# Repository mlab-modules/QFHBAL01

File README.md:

# QFHBAL01 - Antenna Interface and Balun

The **QFHBAL01** module is an [antenna interface and balun](https://en.wikipedia.org/wiki/Balun) designed for QFH (Quadrifilar Helix) antennas, supporting right-hand (RHCP) and left-hand circular polarizations (LHCP). This module enables efficient impedance matching and balanced transmission in QFH antenna configurations.

## Key Features

- **Polarization**: RHCP and LHCP
- **Frequency Range**: 4.5 - 3000 MHz
- **Insertion Loss**: 2 dB typical
- **Amplitude Balance**: ±1 dB
- **Phase Balance**: ±20°
- **Power Rating**: 250 mW max RF, 30 mA max DC
- **Operating Temperature**: -55 °C to +85 °C
- **Dimensions**: Diameter 32 mm, Height 20 mm
- **Weight**: 10 g

## Transformer Mounting Options

The **ETC1-1-13** transformer on the QFHBAL01 module can be soldered onto the PCB in two configurations:

1. **Galvanic Isolation**: Isolates the antenna from the RF line, enhancing protection for the receiver input but potentially increasing insertion loss slightly.
2. **Direct Galvanic Connection**: Connects the antenna directly to the RF line without isolation, minimizing insertion loss but offering less protection for the receiver input.

These configurations allow customization based on application requirements for input protection and insertion loss.

### Balun Polarization and Connection

| Helices     | Feedpoint      | Radiation | Polarization |
|-------------|----------------|-----------|--------------|
| Left-hand   | Standard       | Upward    | RHCP         |
| Right-hand  | Anti-standard  | Upward    | LHCP         |
| Left-hand   | Anti-standard  | Downward  | RHCP         |
| Right-hand  | Standard       | Downward  | LHCP         |

*Source: [QHA Simulation](https://uuki.kapsi.fi/qha_simul.html)*

## Schematic and Mechanical Drawing

- [Schematic (PDF)](/doc/gen/QFHBAL01-schematic.pdf)
- [Mechanical Drawing (PDF)](/doc/src/img/dimensions.png)

### ETC1-1-13 Transformer Specifications

The **ETC1-1-13** transformer offers a 1:1 impedance ratio suitable for balanced RF transmission:

- **Frequency Range**: 4.5 - 3000 MHz
- **Insertion Loss**: 0.32 dB typical, max 3.5 dB at high frequencies
- **Amplitude Balance**: ±1 dB
- **Phase Balance**: ±20°
- **Power Rating**: 250 mW max
- **Operating Temperature**: -55°C to +85°C

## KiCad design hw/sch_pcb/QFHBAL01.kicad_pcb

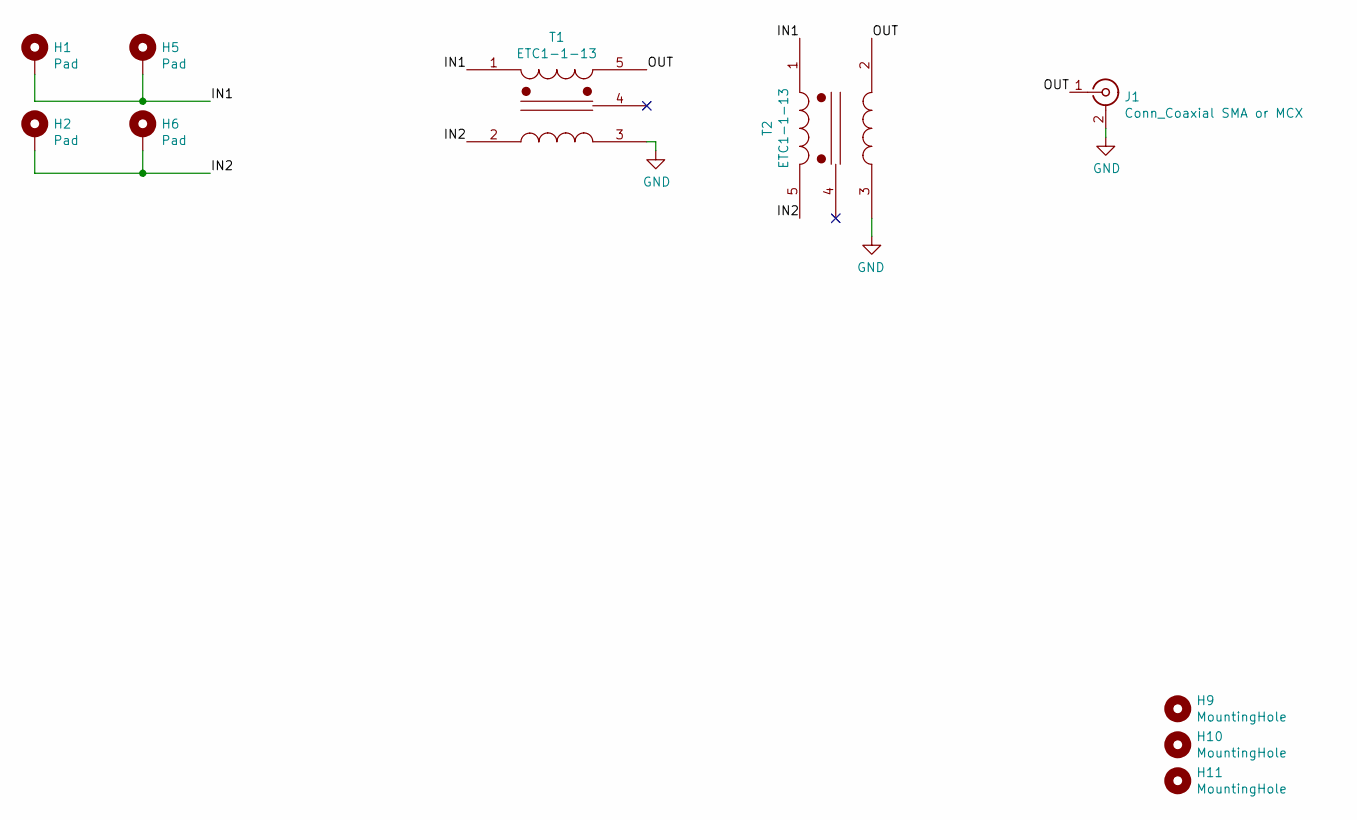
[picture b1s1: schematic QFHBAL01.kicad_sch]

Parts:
H1, H2, H5, H6: Pad; MountingHole_2.2mm_M2_Pad
H9, H10, H11: MountingHole; MountingHole_3.2mm_M3
J1: Conn_Coaxial SMA or MCX; SMA_Amphenol_901-144_Vertical
T1, T2: ETC1-1-13; Transformer_MACOM_SM-22

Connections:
/IN1: H1.1, H5.1, T1.1 (AA), T2.1 (AA)
/IN2: H2.1, H6.1, T1.2 (AB), T2.5 (SB)
/OUT: J1.1 (In), T1.5 (SB), T2.2 (AB)
GND: J1.2 (Ext), T1.3 (SA), T2.3 (SA)

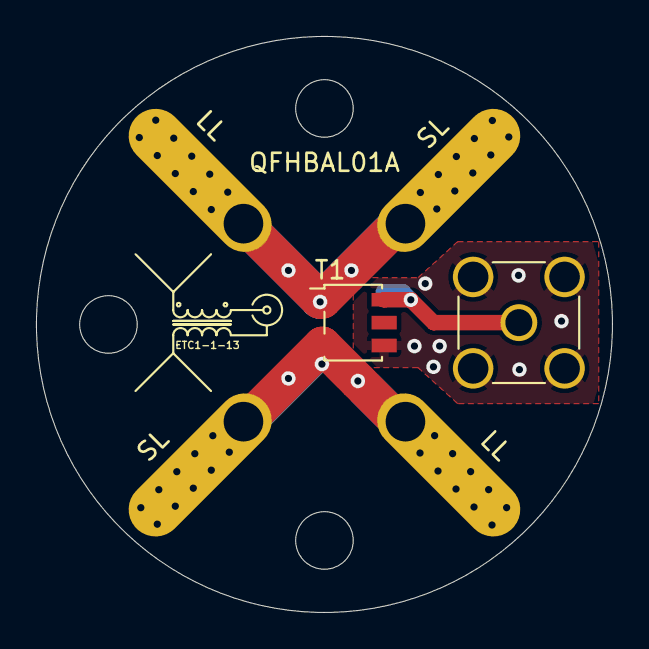
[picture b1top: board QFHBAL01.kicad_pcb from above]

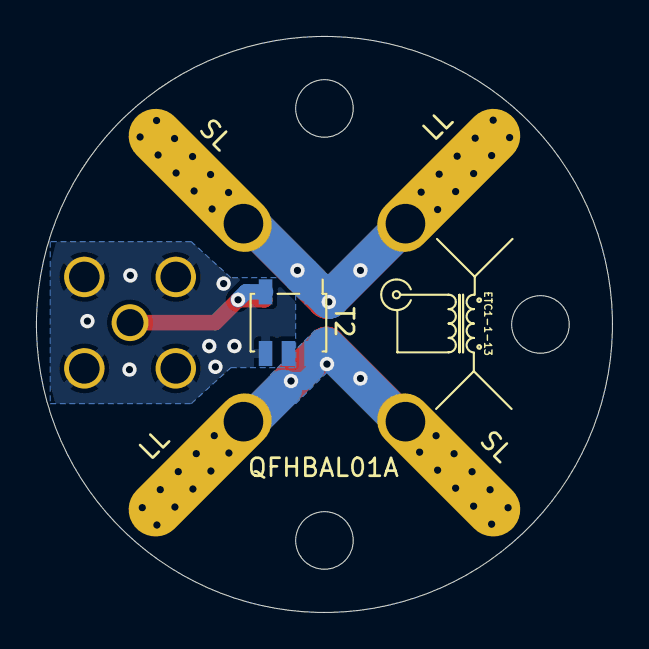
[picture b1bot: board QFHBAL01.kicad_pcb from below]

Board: 2 copper layers, 32.0 x 32.0 mm, 10 parts (3 on the bottom side), 4 nets.

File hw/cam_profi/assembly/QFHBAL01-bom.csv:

Component,Description,Part,References,Value,Footprint,Quantity Per PCB,Datasheet
1,"coaxial connector (BNC, SMA, SMB, SMC, Cinch/RCA, ...)",Conn_Coaxial,J1,Conn_Coaxial SMA or MCX,SMA_Amphenol_901-144_Vertical,1, ~
2,,ETC1-1-13-riske-symbols,T1T2,ETC1-1-13,Transformer_MACOM_SM-22,2,https://www.minicircuits.com/pdfs/TC1-1-13MX+.pdf

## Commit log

2022-04-06 automated commit; add github actions
2022-04-06 Update actions products
2023-05-25 Update metadata files
2023-05-28 Update workflow files
2023-07-05 automated commit; rename source files to new naming convence
2023-07-05 some comment
2023-07-05 aktualizace .gitmodules
2023-09-16 Update image to image_title
2023-09-16 Update status
2024-11-07 update assets, save in KiCADv8
2024-11-07 update actions
2024-11-13 Improved readme documentation.
